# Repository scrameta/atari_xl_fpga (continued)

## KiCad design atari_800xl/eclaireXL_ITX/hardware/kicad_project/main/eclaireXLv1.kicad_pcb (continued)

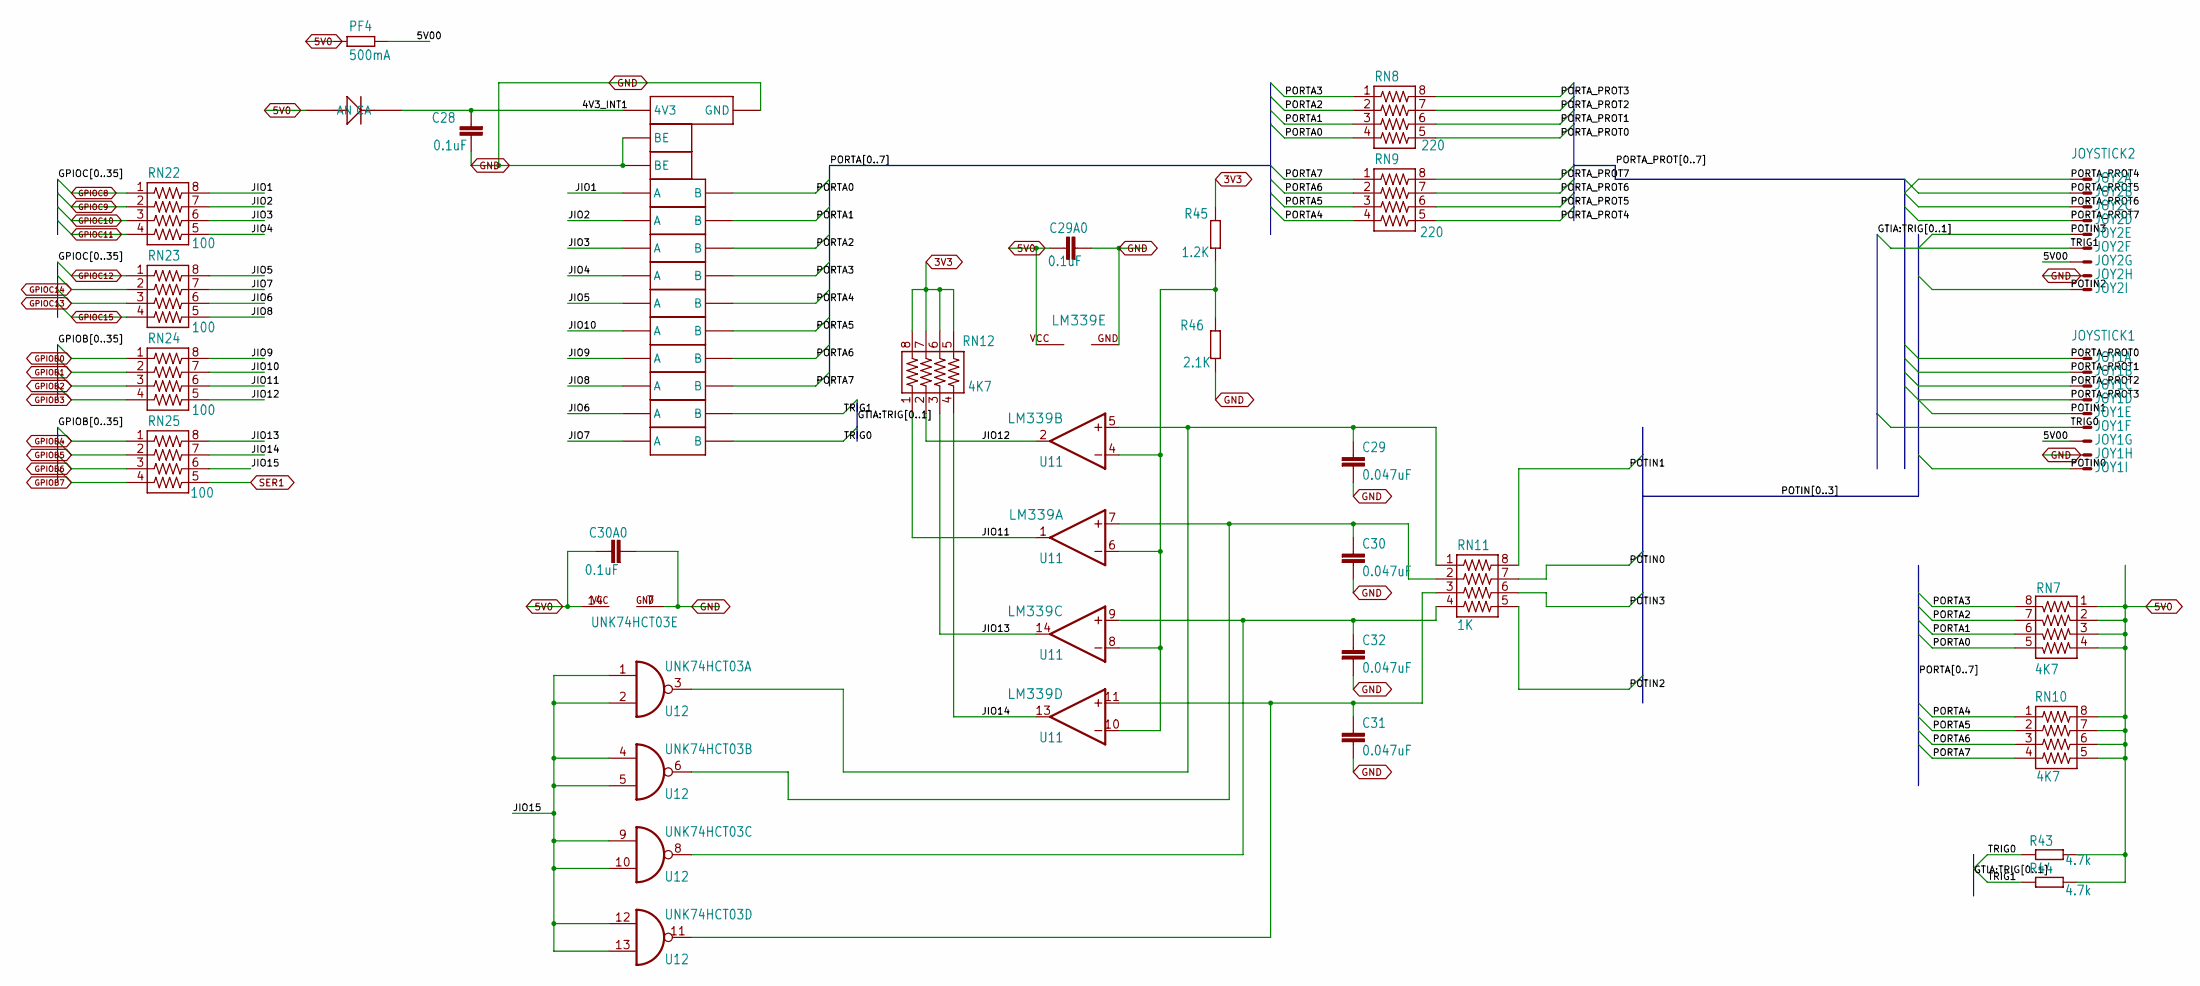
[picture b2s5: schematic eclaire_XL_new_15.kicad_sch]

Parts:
C28, C29A0, C30A0: 0.1uF; C0805K
C29, C30, C31, C32: 0.047uF; C0805K
D2: 1N4148; SOD123
IC5: U10; TSSOP24
JOY1: JOYSTICK1; M09HP
JOY2: JOYSTICK2; M09HP
LM339: U11; TSSOP-14
PF4: 500mA; R1206
R43, R44: 4.7k; M0805
R45: 1.2K; R0805
R46: 2.1K; R0805
RN7, RN10, RN12: 4K7; 743-8
RN8, RN9: 220; 743-8
RN11: 1K; 743-8
RN22, RN23, RN24, RN25: 100; 743-8
UNK74HCT03: U12; SO14

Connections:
3V3: R45.2, RN12.5, RN12.6, RN12.7, RN12.8; also elsewhere on the board
4V3_INT1: C28.2, D2.1 (CA), IC5.24 (4V3)
5V0: C29A0.1, C30A0.1, D2.2 (AN), LM339.3 (VCC), PF4.1, R43.2, R44.2, RN7.1, RN7.2, RN7.3, RN7.4, RN10.5, RN10.6, RN10.7, RN10.8, UNK74HCT03.14 (VCC); also elsewhere on the board
5V00: JOY1.7, JOY2.7, PF4.2
GPIOB0: RN24.1; also elsewhere on the board
GPIOB1: RN24.2; also elsewhere on the board
GPIOB2: RN24.3; also elsewhere on the board
GPIOB3: RN24.4; also elsewhere on the board
GPIOB4: RN25.1; also elsewhere on the board
GPIOB5: RN25.2; also elsewhere on the board
GPIOB6: RN25.3; also elsewhere on the board
GPIOB7: RN25.4; also elsewhere on the board
GPIOC8: RN22.1; also elsewhere on the board
GPIOC9: RN22.2; also elsewhere on the board
GPIOC10: RN22.3; also elsewhere on the board
GPIOC11: RN22.4; also elsewhere on the board
GPIOC12: RN23.1; also elsewhere on the board
GPIOC13: RN23.3; also elsewhere on the board
GPIOC14: RN23.2; also elsewhere on the board
GPIOC15: RN23.4; also elsewhere on the board
JIO1: IC5.3 (A), RN22.8
JIO2: IC5.4 (A), RN22.7
JIO3: IC5.7 (A), RN22.6
JIO4: IC5.8 (A), RN22.5
JIO5: IC5.11 (A), RN23.8
JIO6: IC5.21 (A), RN23.6
JIO7: IC5.22 (A), RN23.7
JIO8: IC5.18 (A), RN23.5
JIO9: IC5.17 (A), RN24.8
JIO10: IC5.14 (A), RN24.7
JIO11: LM339.1 (OUT), RN12.1, RN24.6
JIO12: LM339.2 (OUT), RN12.2, RN24.5
JIO13: LM339.14 (OUT), RN12.3, RN25.8
JIO14: LM339.13 (OUT), RN12.4, RN25.7
JIO15: RN25.6, UNK74HCT03.1 (I0), UNK74HCT03.2 (I1), UNK74HCT03.4 (I0), UNK74HCT03.5 (I1), UNK74HCT03.9 (I0), UNK74HCT03.10 (I1), UNK74HCT03.12 (I0), UNK74HCT03.13 (I1)
unnamed: LM339.4 (-IN), LM339.6 (-IN), LM339.8 (-IN), LM339.10 (-IN), R45.1, R46.2
PORTA0: IC5.2 (B), RN7.5, RN8.4
PORTA1: IC5.5 (B), RN7.6, RN8.3
PORTA2: IC5.6 (B), RN7.7, RN8.2
PORTA3: IC5.9 (B), RN7.8, RN8.1
PORTA4: IC5.10 (B), RN9.4, RN10.1
PORTA5: IC5.15 (B), RN9.3, RN10.2
PORTA6: IC5.16 (B), RN9.2, RN10.3
PORTA7: IC5.19 (B), RN9.1, RN10.4
PORTA_PROT0: JOY1.1, RN8.5
PORTA_PROT1: JOY1.2, RN8.6
PORTA_PROT2: JOY1.3, RN8.7
PORTA_PROT3: JOY1.4, RN8.8
PORTA_PROT4: JOY2.1, RN9.5
PORTA_PROT5: JOY2.2, RN9.6
PORTA_PROT6: JOY2.3, RN9.7
PORTA_PROT7: JOY2.4, RN9.8
POT0: C29.1, LM339.5 (+IN), RN11.1, UNK74HCT03.3 (O)
POT1: C30.1, LM339.7 (+IN), RN11.2, UNK74HCT03.6 (O)
POT2: C32.1, LM339.9 (+IN), RN11.4, UNK74HCT03.8 (O)
POT3: C31.1, LM339.11 (+IN), RN11.3, UNK74HCT03.11 (O)
POTIN0: JOY1.9, RN11.7
POTIN1: JOY1.5, RN11.8
POTIN2: JOY2.9, RN11.5
POTIN3: JOY2.5, RN11.6
SER1: RN25.5; also elsewhere on the board
TRIG0: IC5.23 (B), JOY1.6, R43.1
TRIG1: IC5.20 (B), JOY2.6, R44.1

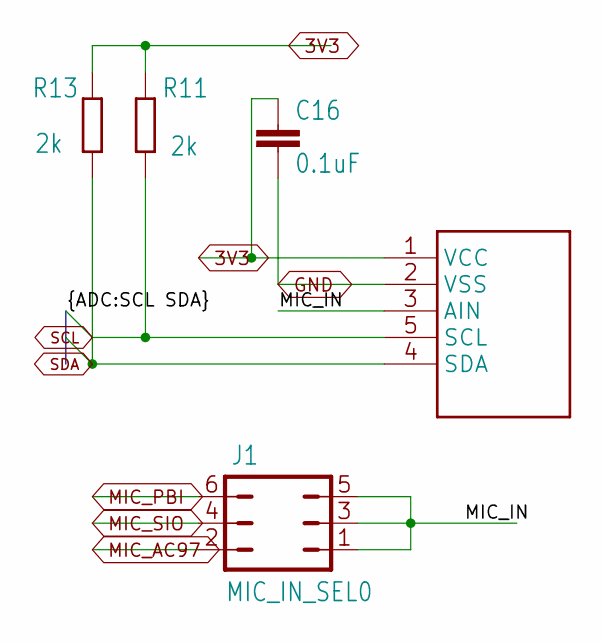
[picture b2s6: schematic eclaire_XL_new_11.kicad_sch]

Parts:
ADC0: U4; SOT95P280X145-5N
C16: 0.1uF; C0805
MIC_IN_SEL0: J1; JP3Q
R11, R13: 2k; M0805

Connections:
3V3: ADC0.1 (VCC), C16.1, R11.1, R13.2; also elsewhere on the board
MIC_AC97: MIC_IN_SEL0.2; also elsewhere on the board
MIC_IN: ADC0.3 (AIN), MIC_IN_SEL0.1, MIC_IN_SEL0.3, MIC_IN_SEL0.5
MIC_PBI: MIC_IN_SEL0.6; also elsewhere on the board
MIC_SIO: MIC_IN_SEL0.4; also elsewhere on the board

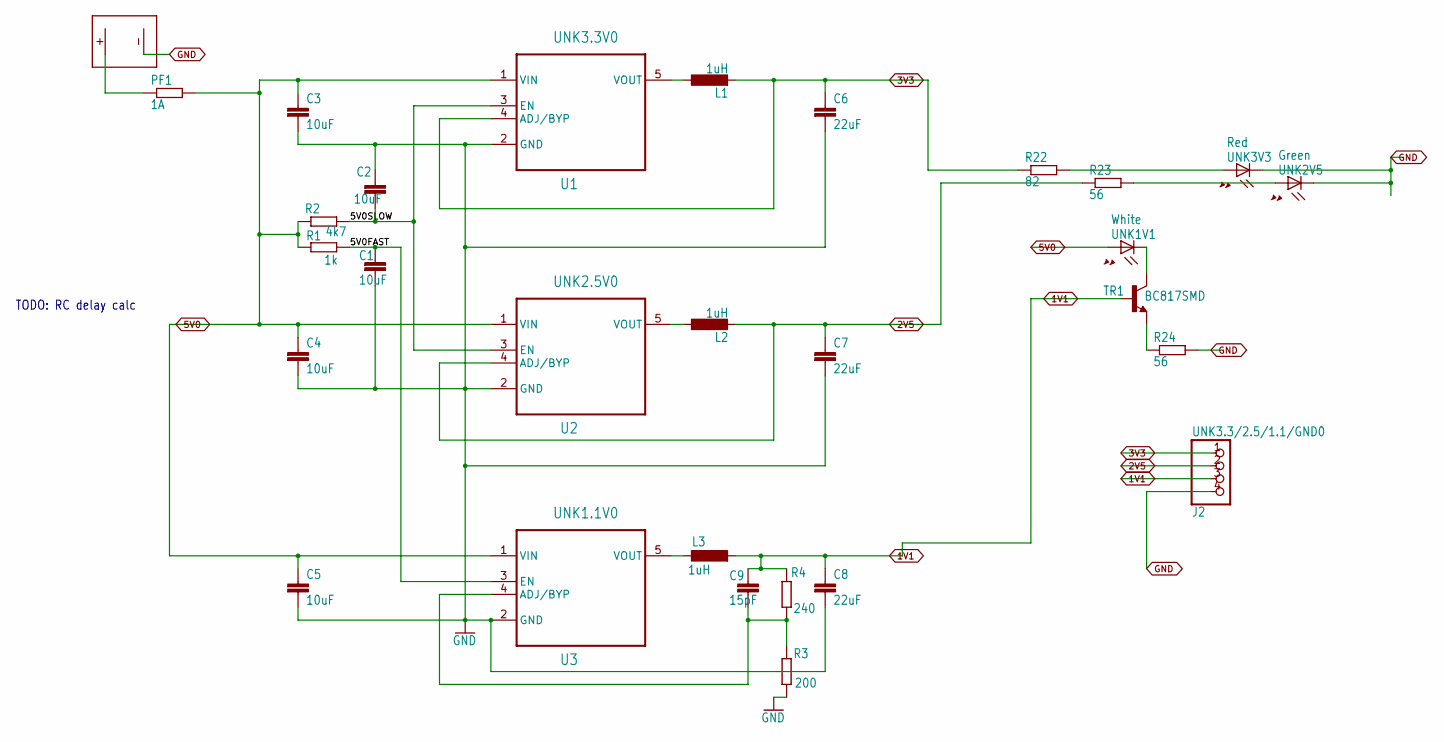
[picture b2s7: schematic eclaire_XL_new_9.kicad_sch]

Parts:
C1, C2, C3, C4, C5: 10uF; C0805
C6, C7, C8: 22uF; C0805
C9: 15pF; C0805
L1, L2, L3: 1uH; L3225M
PF1: 1A; R1206
R1: 1k; R0805
R2: 4k7; R0805
R3: 200; R0805
R4: 240; R0805
R22: 82; R0805
R23, R24: 56; R0805
TR1: BC817SMD; SOT23-BEC
U$6: MOLEX_PS
UNK1.1V0: U3; SOT95P280X145-5N
UNK1V1: White; CHIP-LED0805
UNK2.5V0: U2; SOT95P280X145-5N
UNK2V5: Green; CHIP-LED0805
UNK3.3/2.5/1.1/GND0: J2; 1X04
UNK3.3V0: U1; SOT95P280X145-5N
UNK3V3: Red; CHIP-LED0805

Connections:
1V1: C8.1, C9.1, L3.2, R4.2, TR1.B, UNK3.3/2.5/1.1/GND0.3; also elsewhere on the board
2V5: C7.1, L2.2, R23.2, UNK2.5V0.4 (ADJ/BYP), UNK3.3/2.5/1.1/GND0.2; also elsewhere on the board
3V3: C6.1, L1.2, R22.2, UNK3.3/2.5/1.1/GND0.1, UNK3.3V0.4 (ADJ/BYP); also elsewhere on the board
5V0: C3.1, C4.1, C5.1, PF1.2, R1.1, R2.1, UNK1.1V0.1 (VIN), UNK1V1.A, UNK2.5V0.1 (VIN), UNK3.3V0.1 (VIN); also elsewhere on the board
5V0FAST: C1.1, R1.2, UNK1.1V0.3 (EN)
5V0SLOW: C2.2, R2.2, UNK2.5V0.3 (EN), UNK3.3V0.3 (EN)
unnamed: PF1.1, U$6.+
unnamed: R22.1, UNK3V3.A
unnamed: R23.1, UNK2V5.A
unnamed: TR1.C, UNK1V1.C
unnamed: R24.1, TR1.E
unnamed: L3.1, UNK1.1V0.5 (VOUT)
unnamed: L2.1, UNK2.5V0.5 (VOUT)
unnamed: L1.1, UNK3.3V0.5 (VOUT)
unnamed: C9.2, R3.2, R4.1, UNK1.1V0.4 (ADJ/BYP)

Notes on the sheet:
TODO: RC delay calc

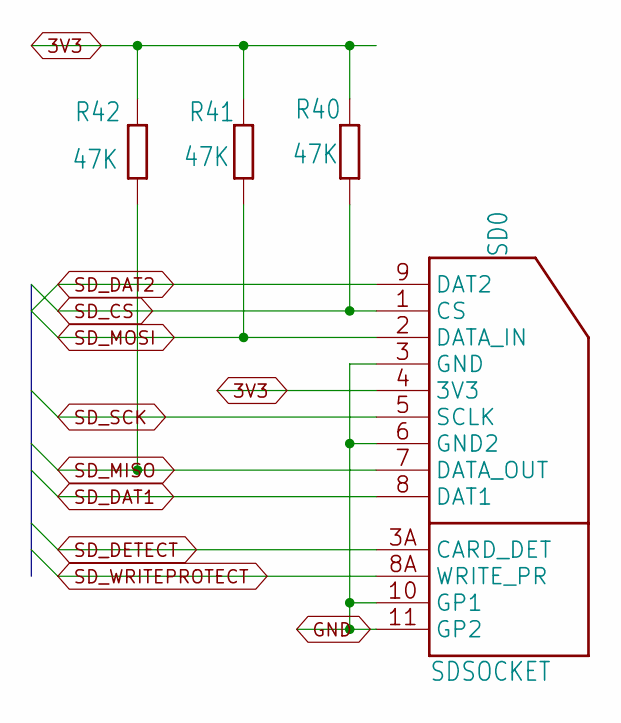
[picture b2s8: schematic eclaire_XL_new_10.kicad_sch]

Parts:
R40, R41, R42: 47K; M0805
SD0: SDSOCKET

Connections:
3V3: R40.2, R41.2, R42.2, SD0.4 (3V3); also elsewhere on the board
SD_CS: R40.1, SD0.1 (CS); also elsewhere on the board
SD_DAT1: SD0.8 (DAT1); also elsewhere on the board
SD_DAT2: SD0.9 (DAT2); also elsewhere on the board
SD_DETECT: SD0.3A (CARD_DET); also elsewhere on the board
SD_MISO: R42.1, SD0.7 (DATA_OUT); also elsewhere on the board
SD_MOSI: R41.1, SD0.2 (DATA_IN); also elsewhere on the board
SD_SCK: SD0.5 (SCLK); also elsewhere on the board
SD_WRITEPROTECT: SD0.8A (WRITE_PR); also elsewhere on the board

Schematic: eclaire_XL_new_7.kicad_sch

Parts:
PF2: 500mA; R1206
R25, R27, R29, R31: 22; R0805
R26, R28, R30, R32: 15k; R0805
USB_A_B0: ML10
X1, X3: USB-A-H

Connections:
5V0: PF2.1; also elsewhere on the board
unnamed: PF2.2, USB_A_B0.1, USB_A_B0.2, X1.VBUS, X3.VBUS
unnamed: R25.2, R26.1, USB_A_B0.5, X1.D+
unnamed: R27.2, R28.1, USB_A_B0.3, X1.D-
unnamed: R29.2, R30.1, USB_A_B0.6, X3.D+
unnamed: R31.2, R32.1, USB_A_B0.4, X3.D-
USB1DM: R27.1; also elsewhere on the board
USB1DP: R25.1; also elsewhere on the board
USB2DM: R31.1; also elsewhere on the board
USB2DP: R29.1; also elsewhere on the board

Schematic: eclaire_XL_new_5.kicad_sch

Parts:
GPIO_A0: ML40E; ML40
GPIO_B0: ML14
RN13, RN14, RN15, RN16, RN17, RN18, RN19, RN20, RN21, RN26, RN27, RN28: 100; 743-8
U$5: HDR_SMALL_36_DEV_LALIGNED; HDR_141_36

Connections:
3V3: GPIO_A0.29, GPIO_B0.13; also elsewhere on the board
5V0: GPIO_A0.11, GPIO_B0.14; also elsewhere on the board
EXP1: GPIO_B0.1, RN26.6
EXP2: GPIO_B0.2, RN26.5
EXP3: GPIO_B0.3, RN27.8
EXP4: GPIO_B0.4, RN27.7
EXP5: GPIO_B0.5, RN27.6
EXP6: GPIO_B0.6, RN27.5
EXP7: GPIO_B0.7, RN28.8
EXP8: GPIO_B0.8, RN28.7
EXP9: GPIO_B0.9, RN28.6
EXP10: GPIO_B0.10, RN28.5
GPIOA0: RN13.1, U$5.P$1 (GPIO_0); also elsewhere on the board
GPIOA1: RN13.2, U$5.P$2 (GPIO_1); also elsewhere on the board
GPIOA2: RN13.3, U$5.P$3 (GPIO_2); also elsewhere on the board
GPIOA3: RN13.4, U$5.P$4 (GPIO_3); also elsewhere on the board
GPIOA4: RN14.1, U$5.P$5 (GPIO_4); also elsewhere on the board
GPIOA5: RN14.2, U$5.P$6 (GPIO_5); also elsewhere on the board
GPIOA6: RN14.3, U$5.P$7 (GPIO_6); also elsewhere on the board
GPIOA7: RN14.4, U$5.P$8 (GPIO_7); also elsewhere on the board
GPIOA8: RN15.1, U$5.P$9 (GPIO_8); also elsewhere on the board
GPIOA9: RN15.2, U$5.P$10 (GPIO_9); also elsewhere on the board
GPIOA10: RN15.3, U$5.P$11 (GPIO_10); also elsewhere on the board
GPIOA11: RN15.4, U$5.P$12 (GPIO_11); also elsewhere on the board
GPIOA12: RN16.1, U$5.P$13 (GPIO_12); also elsewhere on the board
GPIOA13: RN16.2, U$5.P$14 (GPIO_13); also elsewhere on the board
GPIOA14: RN16.3, U$5.P$15 (GPIO_14); also elsewhere on the board
GPIOA15: RN16.4, U$5.P$16 (GPIO_15); also elsewhere on the board
GPIOA16: RN17.1, U$5.P$17 (GPIO_16); also elsewhere on the board
GPIOA17: RN17.2, U$5.P$18 (GPIO_17); also elsewhere on the board
GPIOA18: RN17.3, U$5.P$19 (GPIO_18); also elsewhere on the board
GPIOA19: RN17.4, U$5.P$20 (GPIO_19); also elsewhere on the board
GPIOA20: RN18.1, U$5.P$21 (GPIO_20); also elsewhere on the board
GPIOA21: RN18.2, U$5.P$22 (GPIO_21); also elsewhere on the board
GPIOA22: RN18.3, U$5.P$23 (GPIO_22); also elsewhere on the board
GPIOA23: RN18.4, U$5.P$24 (GPIO_23); also elsewhere on the board
GPIOA24: RN19.1, U$5.P$25 (GPIO_24); also elsewhere on the board
GPIOA25: RN19.2, U$5.P$26 (GPIO_25); also elsewhere on the board
GPIOA26: RN19.3, U$5.P$27 (GPIO_26); also elsewhere on the board
GPIOA27: RN19.4, U$5.P$28 (GPIO_27); also elsewhere on the board
GPIOA28: RN20.1, U$5.P$29 (GPIO_28); also elsewhere on the board
GPIOA29: RN20.2, U$5.P$30 (GPIO_29); also elsewhere on the board
GPIOA30: RN20.3, U$5.P$31 (GPIO_30); also elsewhere on the board
GPIOA31: RN20.4, U$5.P$32 (GPIO_31); also elsewhere on the board
GPIOA32: RN21.1, U$5.P$33 (GPIO_32); also elsewhere on the board
GPIOA33: RN21.2, U$5.P$34 (GPIO_33); also elsewhere on the board
GPIOA34: RN21.3, U$5.P$35 (GPIO_34); also elsewhere on the board
GPIOA35: RN21.4, U$5.P$36 (GPIO_35); also elsewhere on the board
GPIOB8: RN26.1; also elsewhere on the board
GPIOB9: RN26.2; also elsewhere on the board
GPIOB10: RN26.3; also elsewhere on the board
GPIOB11: RN26.4; also elsewhere on the board
GPIOB12: RN27.1; also elsewhere on the board
GPIOB13: RN27.2; also elsewhere on the board
GPIOB14: RN27.3; also elsewhere on the board
GPIOB15: RN27.4; also elsewhere on the board
GPIOC16: RN28.2; also elsewhere on the board
GPIOC18: RN28.3; also elsewhere on the board
GPIOC19: RN28.4; also elsewhere on the board
unnamed: GPIO_A0.1, RN13.8
unnamed: GPIO_A0.2, RN13.7
unnamed: GPIO_A0.3, RN13.6
unnamed: GPIO_A0.4, RN13.5
unnamed: GPIO_A0.5, RN14.8
unnamed: GPIO_A0.6, RN14.7
unnamed: GPIO_A0.7, RN14.6
unnamed: GPIO_A0.8, RN14.5
unnamed: GPIO_A0.9, RN15.8
unnamed: GPIO_A0.10, RN15.7
unnamed: GPIO_A0.13, RN15.6
unnamed: GPIO_A0.14, RN15.5
unnamed: GPIO_A0.15, RN16.8
unnamed: GPIO_A0.17, RN16.6
unnamed: GPIO_A0.16, RN16.7
unnamed: GPIO_A0.18, RN16.5
unnamed: GPIO_A0.19, RN17.8
unnamed: GPIO_A0.20, RN17.7
unnamed: GPIO_A0.21, RN17.6
unnamed: GPIO_A0.22, RN17.5
unnamed: GPIO_A0.23, RN18.8
unnamed: GPIO_A0.25, RN18.6
unnamed: GPIO_A0.24, RN18.7
unnamed: GPIO_A0.26, RN18.5
unnamed: GPIO_A0.27, RN19.8
unnamed: GPIO_A0.28, RN19.7
unnamed: GPIO_A0.31, RN19.6
unnamed: GPIO_A0.32, RN19.5
unnamed: GPIO_A0.33, RN20.8
unnamed: GPIO_A0.34, RN20.7
unnamed: GPIO_A0.35, RN20.6
unnamed: GPIO_A0.36, RN20.5
unnamed: GPIO_A0.37, RN21.8
unnamed: GPIO_A0.38, RN21.7
unnamed: GPIO_A0.39, RN21.6
unnamed: GPIO_A0.40, RN21.5
SER2: RN26.8; also elsewhere on the board
SER3: RN26.7; also elsewhere on the board

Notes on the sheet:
Resistors~

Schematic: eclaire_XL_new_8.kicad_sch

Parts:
C12, C14: 0.1uF; C0805
C13: 0.01uF; C0805
C15: 10uF; C0805

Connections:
3V3: C12.1, C13.1, C14.1, C15.1; also elsewhere on the board

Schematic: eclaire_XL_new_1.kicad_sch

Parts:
C17, C27: 0.1uF; C0805
JTAG0: ML10
R12, R17, R18: 10k; M0805
R14: 2K 1%; M0805
R15, R16: 4.7k; M0805
R19, R21: 1k-10k; M0805
R20: 1k; M0805
R25A0: 560; M0805
RESET0: RESET; JP1
RESET_LED0: RESET; JP1
SPI0: U6; EPCS_BOTH
U$1: U7; CYCLONEVF484V2
XTL_50MHZ0: 50MHz; SG-636

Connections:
1V1: U$1.J4 (VCC), U$1.J10 (VCC), U$1.J12 (VCC), U$1.J14 (VCC), U$1.J16 (VCC), U$1.K3 (VCC), U$1.K5 (VCC), U$1.K11 (VCC), U$1.K13 (VCC), U$1.K15 (VCC), U$1.L4 (VCC), U$1.L10 (VCC), U$1.L12 (VCC), U$1.L14 (VCC), U$1.L16 (VCC), U$1.M11 (VCC), U$1.M13 (VCC), U$1.M15 (VCC), U$1.N4 (VCC), U$1.N10 (VCC), U$1.N12 (VCC), U$1.N14 (VCC), U$1.P3 (VCC), U$1.P11 (VCC), U$1.P13 (VCC), U$1.P15 (VCC); also elsewhere on the board
2V5: U$1.A3 (VCCBAT), U$1.D11 (VCC_AUX), U$1.D18 (VCC_AUX), U$1.E6 (VCC_AUX), U$1.F4 (VCCA_FPLL), U$1.H19 (VCCA_FPLL), U$1.M3 (VCCA_FPLL), U$1.T3 (VCCA_FPLL), U$1.T5 (VCCA_FPLL), U$1.U18 (VCCA_FPLL), U$1.W7 (VCC_AUX), U$1.W13 (VCC_AUX), U$1.W18 (VCC_AUX); also elsewhere on the board
3V3: C17.1, C27.1, JTAG0.4, R12.2, R15.1, R16.1, R17.2, R18.2, R19.2, R21.2, SPI0.8 (VCC), SPI0.L$2 (VCC), U$1.A6 (VCCIO), U$1.A16 (VCCIO), U$1.AA16 (VCCIO), U$1.AA21 (VCCIO), U$1.AB16 (VREF), U$1.B8 (VREF), U$1.B19 (VCCIO), U$1.C7 (VCCIO), U$1.C10 (VCCPGM), U$1.C12 (VCCIO), U$1.C14 (VREF), U$1.C22 (VCCIO), U$1.D4 (VCCIO), U$1.D8 (VCCPGM), U$1.D14 (VCCPGM), U$1.D15 (VCCIO), U$1.D16 (VCCPGM), U$1.E1 (VCCPGM), U$1.E8 (VCCIO), U$1.E11 (VCCPGM), U$1.E18 (VCCIO), U$1.F3 (MSEL_4), U$1.F8 (VCCPGM), U$1.F11 (VCCIO), U$1.F21 (VCCIO), U$1.G7 (VCCIO), U$1.G14 (VCCIO), U$1.H17 (VCCIO), U$1.J1 (VCCIO), U$1.J2 (VCCPGM), U$1.J6 (MSEL_1), U$1.K18 (VCCIO), U$1.L6 (MSEL_0), U$1.L20 (VREF), U$1.M17 (VCCPGM), U$1.M19 (VCCIO), U$1.N18 (VCCPGM), U$1.P20 (VCCIO), U$1.P21 (VCCPGM), U$1.R1 (VCCIO), U$1.R2 (VCCPGM), U$1.R8 (VCCIO), U$1.R18 (VCCIO), U$1.R19 (VCCPGM), U$1.R20 (VREF), U$1.T6 (VCCIO), U$1.T11 (VCCIO), U$1.U14 (VCCIO), U$1.U19 (VCCIO), U$1.V8 (VCCPGM), U$1.W1 (VREF), U$1.W6 (VCCPGM), U$1.W10 (VCCIO), U$1.W11 (VCCPGM), U$1.W12 (VCCPGM), U$1.W14 (VCCPGM), U$1.W15 (VCCIO), U$1.W17 (VCCPGM), U$1.W20 (VCCIO), U$1.Y4 (VCCIO), U$1.Y7 (VREF), U$1.Y8 (VCCIO), U$1.Y12 (VREF), U$1.Y13 (VCCIO), XTL_50MHZ0.P$1 (CON), XTL_50MHZ0.P$4 (VDD); also elsewhere on the board
5V0: R25A0.1; also elsewhere on the board
A0: U$1.R6; also elsewhere on the board
A1: U$1.R5; also elsewhere on the board
A2: U$1.T7; also elsewhere on the board
A3: U$1.U6; also elsewhere on the board
A4: U$1.Y10; also elsewhere on the board
A5: U$1.U10; also elsewhere on the board
A6: U$1.T10; also elsewhere on the board
A7: U$1.AA9; also elsewhere on the board
A8: U$1.W9; also elsewhere on the board
A9: U$1.Y9; also elsewhere on the board
A10: U$1.R7; also elsewhere on the board
A11: U$1.V9; also elsewhere on the board
A12: U$1.T9; also elsewhere on the board
AUDIO_LEFT: U$1.U13; also elsewhere on the board
AUDIO_RIGHT: U$1.T13; also elsewhere on the board
BA0: U$1.P7; also elsewhere on the board
BA1: U$1.P6; also elsewhere on the board
CAS_N: U$1.N8; also elsewhere on the board
CKE: U$1.AB8; also elsewhere on the board
COMMAND: U$1.AB11; also elsewhere on the board
CONFIG_N: R12.1, RESET0.2, U$1.A4 (CONFIG_N)
CONF_DONE: R18.1, U$1.K6 (CONF_DONE)
CS_N: U$1.P8; also elsewhere on the board
DQ0: U$1.K7; also elsewhere on the board
DQ1: U$1.K9; also elsewhere on the board
DQ2: U$1.J7; also elsewhere on the board
DQ3: U$1.J8; also elsewhere on the board
DQ4: U$1.L8; also elsewhere on the board
DQ5: U$1.L7; also elsewhere on the board
DQ6: U$1.M8; also elsewhere on the board
DQ7: U$1.M7; also elsewhere on the board
DQ8: U$1.W8; also elsewhere on the board
DQ9: U$1.T8; also elsewhere on the board
DQ10: U$1.AB7; also elsewhere on the board
DQ11: U$1.AA7; also elsewhere on the board
DQ12: U$1.U7; also elsewhere on the board
DQ13: U$1.AB6; also elsewhere on the board
DQ14: U$1.V6; also elsewhere on the board
DQ15: U$1.AB5; also elsewhere on the board
GPIOA0: U$1.F15; also elsewhere on the board
GPIOA1: U$1.B16; also elsewhere on the board
GPIOA2: U$1.C16; also elsewhere on the board
GPIOA3: U$1.G17; also elsewhere on the board
GPIOA4: U$1.G16; also elsewhere on the board
GPIOA5: U$1.J18; also elsewhere on the board
GPIOA6: U$1.J17; also elsewhere on the board
GPIOA7: U$1.K21; also elsewhere on the board
GPIOA8: U$1.K20; also elsewhere on the board
GPIOA9: U$1.K16; also elsewhere on the board
GPIOA10: U$1.L19; also elsewhere on the board
GPIOA11: U$1.L17; also elsewhere on the board
GPIOA12: U$1.M21; also elsewhere on the board
GPIOA13: U$1.M20; also elsewhere on the board
GPIOA14: U$1.N21; also elsewhere on the board
GPIOA15: U$1.N20; also elsewhere on the board
GPIOA16: U$1.P22; also elsewhere on the board
GPIOA17: U$1.P19; also elsewhere on the board
GPIOA18: U$1.P16; also elsewhere on the board
GPIOA19: U$1.R21; also elsewhere on the board
GPIOA20: U$1.R16; also elsewhere on the board
GPIOA21: U$1.T19; also elsewhere on the board
GPIOA22: U$1.T18; also elsewhere on the board
GPIOA23: U$1.U22; also elsewhere on the board
GPIOA24: U$1.U20; also elsewhere on the board
GPIOA25: U$1.V19; also elsewhere on the board
GPIOA26: U$1.W22; also elsewhere on the board
GPIOA27: U$1.Y22; also elsewhere on the board
GPIOA28: U$1.AA22; also elsewhere on the board
GPIOA29: U$1.AB21; also elsewhere on the board
GPIOA30: U$1.AA20; also elsewhere on the board
GPIOA31: U$1.AA19; also elsewhere on the board
GPIOA32: U$1.Y19; also elsewhere on the board
GPIOA33: U$1.AA18; also elsewhere on the board
GPIOA34: U$1.AB17; also elsewhere on the board
GPIOA35: U$1.U17; also elsewhere on the board
GPIOB0: U$1.G15; also elsewhere on the board
GPIOB1: U$1.E16; also elsewhere on the board
GPIOB2: U$1.D17; also elsewhere on the board
GPIOB3: U$1.G18; also elsewhere on the board
GPIOB4: U$1.H18; also elsewhere on the board
GPIOB5: U$1.J19; also elsewhere on the board
GPIOB6: U$1.K22; also elsewhere on the board
GPIOB7: U$1.K19; also elsewhere on the board
GPIOB8: U$1.K17; also elsewhere on the board
GPIOB9: U$1.L22; also elsewhere on the board
GPIOB10: U$1.L18; also elsewhere on the board
GPIOB11: U$1.M22; also elsewhere on the board
GPIOB12: U$1.M18; also elsewhere on the board
GPIOB13: U$1.M16; also elsewhere on the board
GPIOB14: U$1.N19; also elsewhere on the board
GPIOB15: U$1.N16; also elsewhere on the board
GPIOB16: U$1.P18; also elsewhere on the board
GPIOB17: U$1.P17; also elsewhere on the board
GPIOB18: U$1.R22; also elsewhere on the board
GPIOB19: U$1.R17; also elsewhere on the board
GPIOB20: U$1.T22; also elsewhere on the board
GPIOB21: U$1.T20; also elsewhere on the board
GPIOB22: U$1.T17; also elsewhere on the board
GPIOB23: U$1.U21; also elsewhere on the board
GPIOB24: U$1.V21; also elsewhere on the board
GPIOB25: U$1.V20; also elsewhere on the board
GPIOB26: U$1.W21; also elsewhere on the board
GPIOB27: U$1.Y21; also elsewhere on the board
GPIOB28: U$1.AB22; also elsewhere on the board
GPIOB29: U$1.AB20; also elsewhere on the board
GPIOB30: U$1.Y20; also elsewhere on the board
GPIOB31: U$1.W19; also elsewhere on the board
GPIOB32: U$1.AB18; also elsewhere on the board
GPIOB33: U$1.V18; also elsewhere on the board
GPIOB34: U$1.AA17; also elsewhere on the board
GPIOB35: U$1.Y17; also elsewhere on the board
GPIOC8: U$1.F13; also elsewhere on the board
GPIOC9: U$1.G13; also elsewhere on the board
GPIOC10: U$1.A14; also elsewhere on the board
GPIOC11: U$1.E14; also elsewhere on the board
GPIOC12: U$1.F14; also elsewhere on the board
GPIOC13: U$1.H14; also elsewhere on the board
GPIOC14: U$1.A15; also elsewhere on the board
GPIOC15: U$1.B15; also elsewhere on the board
GPIOC16: U$1.E15; also elsewhere on the board
GPIOC18: U$1.Y16; also elsewhere on the board
GPIOC19: U$1.V16; also elsewhere on the board
GPIOC20: U$1.W16; also elsewhere on the board
GPIOC21: U$1.U16; also elsewhere on the board
GPIOC22: U$1.AB15; also elsewhere on the board
GPIOC23: U$1.AA15; also elsewhere on the board
GPIOC24: U$1.V15; also elsewhere on the board
GPIOC25: U$1.Y15; also elsewhere on the board
GPIOC26: U$1.U15; also elsewhere on the board
GPIOC27: U$1.T15; also elsewhere on the board
GPIOC28: U$1.AA14; also elsewhere on the board
GPIOC29: U$1.V14; also elsewhere on the board
GPIOC30: U$1.Y14; also elsewhere on the board
GPIOC31: U$1.T14; also elsewhere on the board
GPIOC32: U$1.R14; also elsewhere on the board
GPIOC33: U$1.AB13; also elsewhere on the board
GPIOC34: U$1.AA13; also elsewhere on the board
HSYNC: U$1.C11; also elsewhere on the board
MOTOR_RAW: U$1.Y11; also elsewhere on the board
unnamed: SPI0.6 (SCK), SPI0.L$16 (SCK), U$1.V3 (AS_DCLK)
unnamed: SPI0.1 (~CS), SPI0.L$7 (~CS), U$1.R4 (AS_CSO_N)
unnamed: SPI0.2 (SO), SPI0.L$8 (SO), U$1.AB3 (AS_DATA1)
unnamed: SPI0.5 (SI), SPI0.L$15 (SI), U$1.AB4 (AS_DATA0)
unnamed: R16.2, SPI0.3 (~WP), SPI0.L$9 (~WP)
unnamed: R15.2, SPI0.7 (~HOLD), SPI0.L$1 (~HOLD)
unnamed: U$1.H16 (CLK), XTL_50MHZ0.P$3 (OUT)
unnamed: R25A0.2, RESET_LED0.1
PROCEED: U$1.U11; also elsewhere on the board
RAS_N: U$1.N6; also elsewhere on the board
RREF_TL: R14.1, U$1.A1 (RREF_TL)
SDRAM_CLK: U$1.AA8; also elsewhere on the board
SDRAM_LDQM: U$1.M6; also elsewhere on the board
SDRAM_UDQM: U$1.U8; also elsewhere on the board
SD_CS: U$1.D12; also elsewhere on the board
SD_DAT1: U$1.A13; also elsewhere on the board
SD_DAT2: U$1.B12; also elsewhere on the board
SD_DETECT: U$1.E12; also elsewhere on the board
SD_MISO: U$1.C13; also elsewhere on the board
SD_MOSI: U$1.F12; also elsewhere on the board
SD_SCK: U$1.B13; also elsewhere on the board
SD_WRITEPROTECT: U$1.D13; also elsewhere on the board
SIO_CLOCKIN: U$1.AB12; also elsewhere on the board
SIO_CLOCKOUT: U$1.AA12; also elsewhere on the board
SIO_IN: U$1.U12; also elsewhere on the board
SIO_IRQ: U$1.T12; also elsewhere on the board
SIO_OUT: U$1.R12; also elsewhere on the board
STATUS_N: R17.1, U$1.H5 (STATUS_N)
TCK: JTAG0.1, R20.1, U$1.V5 (JTAG_TCK)
TDI: JTAG0.9, R21.1, U$1.W5 (JTAG_TDI)
TDO: JTAG0.3, U$1.M5 (JTAG_TDO)
TMS: JTAG0.5, R19.1, U$1.P5 (JTAG_TMS)
USB1DM: U$1.AA10; also elsewhere on the board
USB1DP: U$1.V10; also elsewhere on the board
USB2DM: U$1.R11; also elsewhere on the board
USB2DP: U$1.AB10; also elsewhere on the board
VGA_B0: U$1.E9; also elsewhere on the board
VGA_B1: U$1.F9; also elsewhere on the board
VGA_B2: U$1.A10; also elsewhere on the board
VGA_B3: U$1.B10; also elsewhere on the board
VGA_B4: U$1.E10; also elsewhere on the board
VGA_B5: U$1.F10; also elsewhere on the board
VGA_B6: U$1.G10; also elsewhere on the board
VGA_B7: U$1.B11; also elsewhere on the board
VGA_BLANK_N: U$1.C9; also elsewhere on the board
VGA_G0: U$1.D7; also elsewhere on the board
VGA_G1: U$1.F7; also elsewhere on the board
VGA_G2: U$1.A8; also elsewhere on the board
VGA_G3: U$1.G8; also elsewhere on the board
VGA_G4: U$1.C8; also elsewhere on the board
VGA_G5: U$1.H8; also elsewhere on the board
VGA_G6: U$1.A9; also elsewhere on the board
VGA_G7: U$1.D9; also elsewhere on the board
VGA_R0: U$1.A5; also elsewhere on the board
VGA_R1: U$1.B5; also elsewhere on the board
VGA_R2: U$1.B6; also elsewhere on the board
VGA_R3: U$1.D6; also elsewhere on the board
VGA_R4: U$1.C6; also elsewhere on the board
VGA_R5: U$1.A7; also elsewhere on the board
VGA_R6: U$1.B7; also elsewhere on the board
VGA_R7: U$1.E7; also elsewhere on the board
VSYNC: U$1.H11; also elsewhere on the board
WE_N: U$1.N9; also elsewhere on the board

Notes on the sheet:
10011 AS 1x/4x
JTAG also used to program AS via special core

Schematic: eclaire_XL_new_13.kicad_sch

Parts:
C20: 0.1uF; C0805K
D1: 1N4148; SOD123
PF3: 500mA; R1206
QS3384: U9; TSSOP24
R33, R34: 2k7; M0805
RN3, RN4: 100; 743-8
RN5, RN6: 4K7; 743-8
S.I.O._INTERFACE0: ML10
TR2: MOT; SOT23-BEC

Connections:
5V0: D1.2 (AN), R33.1, RN5.1, RN5.2, RN5.3, RN5.4, RN6.1, RN6.2, RN6.3, RN6.4, TR2.E; also elsewhere on the board
COMMAND: RN4.2; also elsewhere on the board
MIC_SIO: S.I.O._INTERFACE0.9; also elsewhere on the board
MOTOR_RAW: RN3.1; also elsewhere on the board
unnamed: QS3384.3 (A), RN3.8
unnamed: QS3384.4 (A), RN3.7
unnamed: QS3384.7 (A), RN3.6
unnamed: QS3384.8 (A), RN3.5
unnamed: QS3384.11 (A), RN4.8
unnamed: QS3384.18 (A), RN4.7
unnamed: QS3384.17 (A), RN4.6
unnamed: QS3384.14 (A), RN4.5
unnamed: R34.2, TR2.B
unnamed: QS3384.16 (B), RN5.8, S.I.O._INTERFACE0.4
unnamed: QS3384.15 (B), RN6.6, S.I.O._INTERFACE0.6
unnamed: QS3384.10 (B), RN6.7, S.I.O._INTERFACE0.7
unnamed: QS3384.9 (B), RN6.5, S.I.O._INTERFACE0.5
unnamed: QS3384.6 (B), RN5.7, S.I.O._INTERFACE0.3
unnamed: PF3.2, TR2.C
unnamed: QS3384.2 (B), R33.2, R34.1
unnamed: C20.1, D1.1 (CA), QS3384.24 (4V3)
unnamed: PF3.1, S.I.O._INTERFACE0.8, S.I.O._INTERFACE0.10
PROCEED: RN4.3; also elsewhere on the board
SIO_CLOCKIN: RN4.4; also elsewhere on the board
SIO_CLOCKOUT: RN3.2; also elsewhere on the board
SIO_IN: RN3.3; also elsewhere on the board
SIO_IRQ: RN3.4; also elsewhere on the board
SIO_OUT: RN4.1; also elsewhere on the board

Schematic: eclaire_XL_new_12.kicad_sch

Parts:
H1, H2, H3, H4, H5, H6, H7: MOUNT-PAD-ROUND3.6; 3,6-PAD

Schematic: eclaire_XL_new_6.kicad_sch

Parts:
C19: 0.1uF; C0805
SDRAM0: U8; TSOP54

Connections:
3V3: C19.1, SDRAM0.1 (VDD), SDRAM0.3 (VDDQ), SDRAM0.9 (VDDQ@9), SDRAM0.14 (VDD@14), SDRAM0.27 (VDD@27), SDRAM0.43 (VDDQ@43), SDRAM0.49 (VDDQ@49); also elsewhere on the board
A0: SDRAM0.23 (A0); also elsewhere on the board
A1: SDRAM0.24 (A1); also elsewhere on the board
A2: SDRAM0.25 (A2); also elsewhere on the board
A3: SDRAM0.26 (A3); also elsewhere on the board
A4: SDRAM0.29 (A4); also elsewhere on the board
A5: SDRAM0.30 (A5); also elsewhere on the board
A6: SDRAM0.31 (A6); also elsewhere on the board
A7: SDRAM0.32 (A7); also elsewhere on the board
A8: SDRAM0.33 (A8); also elsewhere on the board
A9: SDRAM0.34 (A9); also elsewhere on the board
A10: SDRAM0.22 (A10/AP); also elsewhere on the board
A11: SDRAM0.35 (A11); also elsewhere on the board
A12: SDRAM0.36 (A12); also elsewhere on the board
BA0: SDRAM0.20 (BA0); also elsewhere on the board
BA1: SDRAM0.21 (BA1); also elsewhere on the board
CAS_N: SDRAM0.17 (CAS#); also elsewhere on the board
CKE: SDRAM0.37 (CKE); also elsewhere on the board
CS_N: SDRAM0.19 (CS#); also elsewhere on the board
DQ0: SDRAM0.2 (DQ0); also elsewhere on the board
DQ1: SDRAM0.4 (DQ1); also elsewhere on the board
DQ2: SDRAM0.5 (DQ2); also elsewhere on the board
DQ3: SDRAM0.7 (DQ3); also elsewhere on the board
DQ4: SDRAM0.8 (DQ4); also elsewhere on the board
DQ5: SDRAM0.10 (DQ5); also elsewhere on the board
DQ6: SDRAM0.11 (DQ6); also elsewhere on the board
DQ7: SDRAM0.13 (DQ7); also elsewhere on the board
DQ8: SDRAM0.42 (DQ8); also elsewhere on the board
DQ9: SDRAM0.44 (DQ9); also elsewhere on the board
DQ10: SDRAM0.45 (DQ10); also elsewhere on the board
DQ11: SDRAM0.47 (DQ11); also elsewhere on the board
DQ12: SDRAM0.48 (DQ12); also elsewhere on the board
DQ13: SDRAM0.50 (DQ13); also elsewhere on the board
DQ14: SDRAM0.51 (DQ14); also elsewhere on the board
DQ15: SDRAM0.53 (DQ15); also elsewhere on the board
RAS_N: SDRAM0.18 (RAS#); also elsewhere on the board
SDRAM_CLK: SDRAM0.38 (CLK); also elsewhere on the board
SDRAM_LDQM: SDRAM0.15 (LDQM); also elsewhere on the board
SDRAM_UDQM: SDRAM0.39 (DQM); also elsewhere on the board
WE_N: SDRAM0.16 (WE#); also elsewhere on the board

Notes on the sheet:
Standard 64 bit wide tssop 54 sram. One like de1 would be good.

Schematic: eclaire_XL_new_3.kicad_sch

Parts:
C10, C11: 0.1uF; C0805
HDMI0: HDMI
JP2: JP2E; JP2
R5: 348; M0805
R6, R7, R8: 75; M0805
R9, R10: 100; R0805
RN1, RN2: 270; 743-8
S-VIDEO_COMP0: MD04SS; MDIN04SS
VGA0: DB15
VIDEODACSA0: U5; QFP50P900X900X120-49N

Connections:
3V3: C11.1, VIDEODACSA0.13 (VAA_2), VIDEODACSA0.29 (VAA_3), VIDEODACSA0.30 (VAA), VIDEODACSA0.38 (~PSAVE); also elsewhere on the board
5V0: HDMI0.18 (+5V); also elsewhere on the board
HSYNC: R10.1; also elsewhere on the board
unnamed: R9.2, VGA0.14
unnamed: R10.2, VGA0.13
unnamed: JP2.3, R6.2, VGA0.1, VIDEODACSA0.34 (IOR)
unnamed: R7.2, S-VIDEO_COMP0.4, VGA0.2, VIDEODACSA0.32 (IOG)
unnamed: C10.1, VIDEODACSA0.36 (VREF)
unnamed: R5.2, VIDEODACSA0.37 (RSET)
unnamed: C11.2, VIDEODACSA0.35 (COMP)
unnamed: HDMI0.1 (TX2_P), RN1.8
unnamed: JP2.1, R8.2, VGA0.3, VIDEODACSA0.28 (IOB)
unnamed: HDMI0.3 (TX2_N), RN1.7
unnamed: HDMI0.4 (TX1_P), RN1.6
unnamed: HDMI0.6 (TX1_N), RN1.5
unnamed: HDMI0.7 (TX0_P), RN2.8
unnamed: HDMI0.9 (TX0_N), RN2.7
unnamed: HDMI0.10 (CLK_P), RN2.6
unnamed: HDMI0.12 (CLK_N), RN2.5
unnamed: JP2.2, S-VIDEO_COMP0.3
VGA_B0: VIDEODACSA0.16 (B0); also elsewhere on the board
VGA_B1: RN2.2, VIDEODACSA0.17 (B1); also elsewhere on the board
VGA_B2: VIDEODACSA0.18 (B2); also elsewhere on the board
VGA_B3: VIDEODACSA0.19 (B3); also elsewhere on the board
VGA_B4: RN2.1, VIDEODACSA0.20 (B4); also elsewhere on the board
VGA_B5: RN2.4, VIDEODACSA0.21 (B5); also elsewhere on the board
VGA_B6: RN2.3, VIDEODACSA0.22 (B6); also elsewhere on the board
VGA_B7: VIDEODACSA0.23 (B7); also elsewhere on the board
VGA_BLANK_N: VIDEODACSA0.11 (~BLANK); also elsewhere on the board
VGA_G0: VIDEODACSA0.3 (G0); also elsewhere on the board
VGA_G1: VIDEODACSA0.4 (G1); also elsewhere on the board
VGA_G2: VIDEODACSA0.5 (G2); also elsewhere on the board
VGA_G3: VIDEODACSA0.6 (G3); also elsewhere on the board
VGA_G4: VIDEODACSA0.7 (G4); also elsewhere on the board
VGA_G5: VIDEODACSA0.8 (G5); also elsewhere on the board
VGA_G6: VIDEODACSA0.9 (G6); also elsewhere on the board
VGA_G7: VIDEODACSA0.10 (G7); also elsewhere on the board
VGA_R0: RN1.1, VIDEODACSA0.41 (R0); also elsewhere on the board
VGA_R1: RN1.2, VIDEODACSA0.42 (R1); also elsewhere on the board
VGA_R2: VIDEODACSA0.43 (R2); also elsewhere on the board
VGA_R3: RN1.4, VIDEODACSA0.44 (R3); also elsewhere on the board
VGA_R4: RN1.3, VIDEODACSA0.45 (R4); also elsewhere on the board
VGA_R5: VIDEODACSA0.46 (R5); also elsewhere on the board
VGA_R6: VIDEODACSA0.47 (R6); also elsewhere on the board
VGA_R7: VIDEODACSA0.48 (R7); also elsewhere on the board
VSYNC: R9.1; also elsewhere on the board

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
